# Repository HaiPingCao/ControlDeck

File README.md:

# ControlDeck

ControlDeck is a simple, multi-purpose, programmable volume knob built with an Arduino Pro Micro.  
It is designed as a compact hardware control interface for volume adjustment, mode switching, and custom hotkeys.

## Hardware

The project uses the following components:

- Arduino Pro Micro
- Rotary encoder with integrated push button
- 4 momentary push buttons
- SSD1306 OLED display (128×64)

### Circuit Setup and Wiring

| Component   | Pin | Description                                  |
| ----------- | --- | -------------------------------------------- |
| Encoder CLK | 5   | Clock signal for rotation detection          |
| Encoder DT  | 4   | Data signal for rotation direction detection |
| Encoder SW  | 6   | Encoder push button                          |
| UP Button   | 10  | Switch to previous mode                      |
| DOWN Button | 16  | Switch to next mode                          |
| # Button    | 14  | Special function button                      |
| \* Button   | 15  | Triggers Win + Ctrl + Alt + F5 hotkey        |

## Software

### Required Libraries

When using the Arduino IDE, install the following libraries via the Arduino Library Manager:

- **HID-Project** by NicoHood
- **Adafruit GFX Library** by Adafruit
- **Adafruit SSD1306** by Adafruit

### Driver Development

A new custom driver written in Rust is currently in early development to support more advanced features.  
See the `mk-driver` directory for details.

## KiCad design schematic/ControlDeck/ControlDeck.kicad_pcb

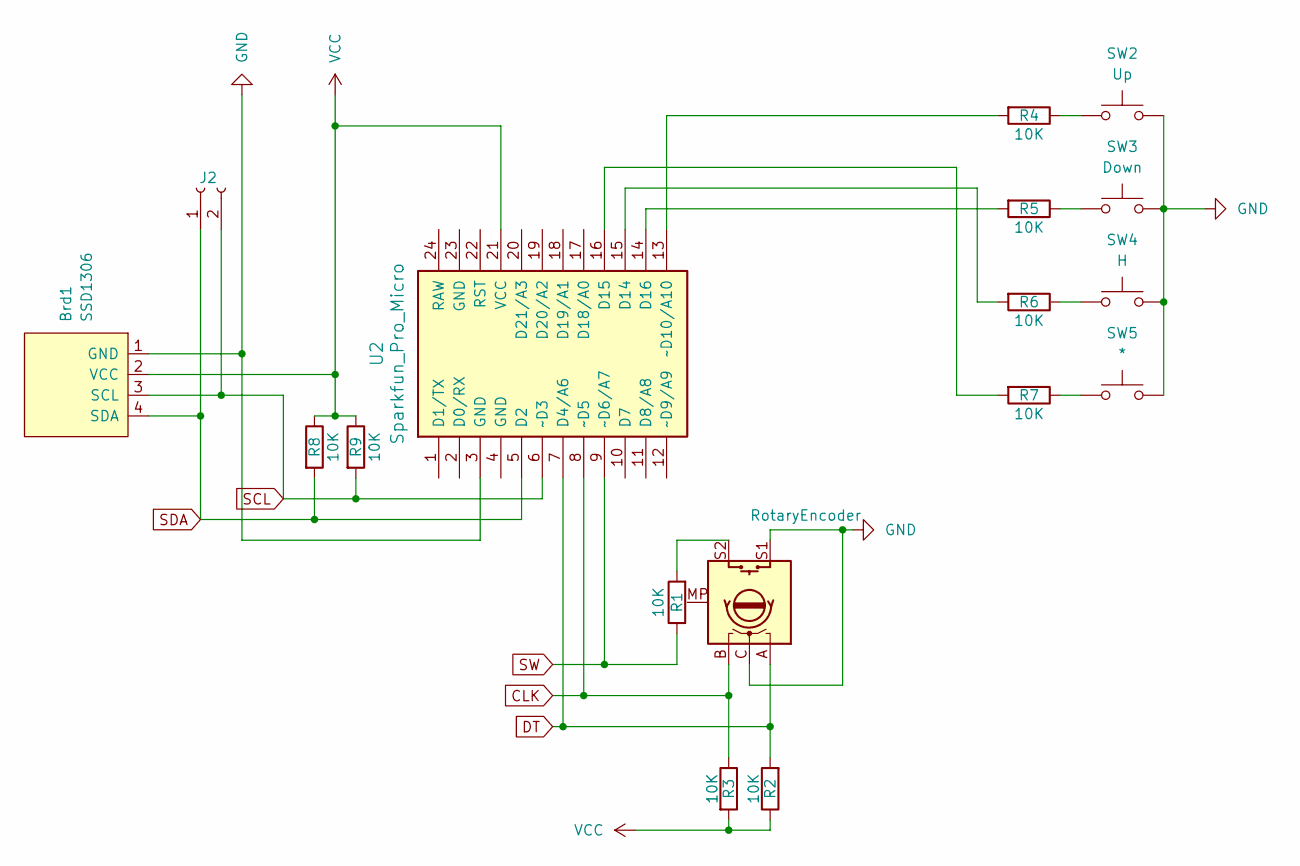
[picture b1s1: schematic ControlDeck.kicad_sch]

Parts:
Brd1: SSD1306; 128x64OLED
J2: Conn_01x02_Socket; JST_PH_B2B-PH-K_1x02_P2.00mm_Vertical
R1, R2, R3, R4, R5, R6, R7, R8, R9: 10K; R_Axial_DIN0204_L3.6mm_D1.6mm_P5.08mm_Horizontal
SW1: RotaryEncoder; RotaryEncoder_Alps_EC11E-Switch_Vertical_H20mm
SW2: Up; SW_SPST_CK_RS282G05A3
SW3: Down; SW_SPST_CK_RS282G05A3
SW4: H; SW_SPST_CK_RS282G05A3
SW5: *; SW_SPST_CK_RS282G05A3
U2: Sparkfun_Pro_Micro

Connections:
CLK: R3.1, SW1.B, U2.8 (~D5)
DT: R2.2, SW1.A, U2.7 (D4/A6)
GND: Brd1.1 (GND), SW1.C, SW1.S1, SW2.2, SW3.2, SW4.2, SW5.2, U2.3 (GND), U2.23 (GND)
unnamed: R1.2, SW1.S2
unnamed: R4.1, SW2.1
unnamed: R5.1, SW3.1
unnamed: R6.1, SW4.1
unnamed: R7.1, SW5.1
unnamed: R6.2, U2.15 (D14)
unnamed: R7.2, U2.16 (D15)
unnamed: R5.2, U2.14 (D16)
unnamed: R4.2, U2.13 (~D10/A10)
SCL: Brd1.3 (SCL), J2.2, R9.2, U2.6 (~D3)
SDA: Brd1.4 (SDA), J2.1, R8.2, U2.5 (D2)
SW: R1.1, U2.9 (~D6/A7)
VCC: Brd1.2 (VCC), R2.1, R3.2, R8.1, R9.1, U2.21 (VCC)

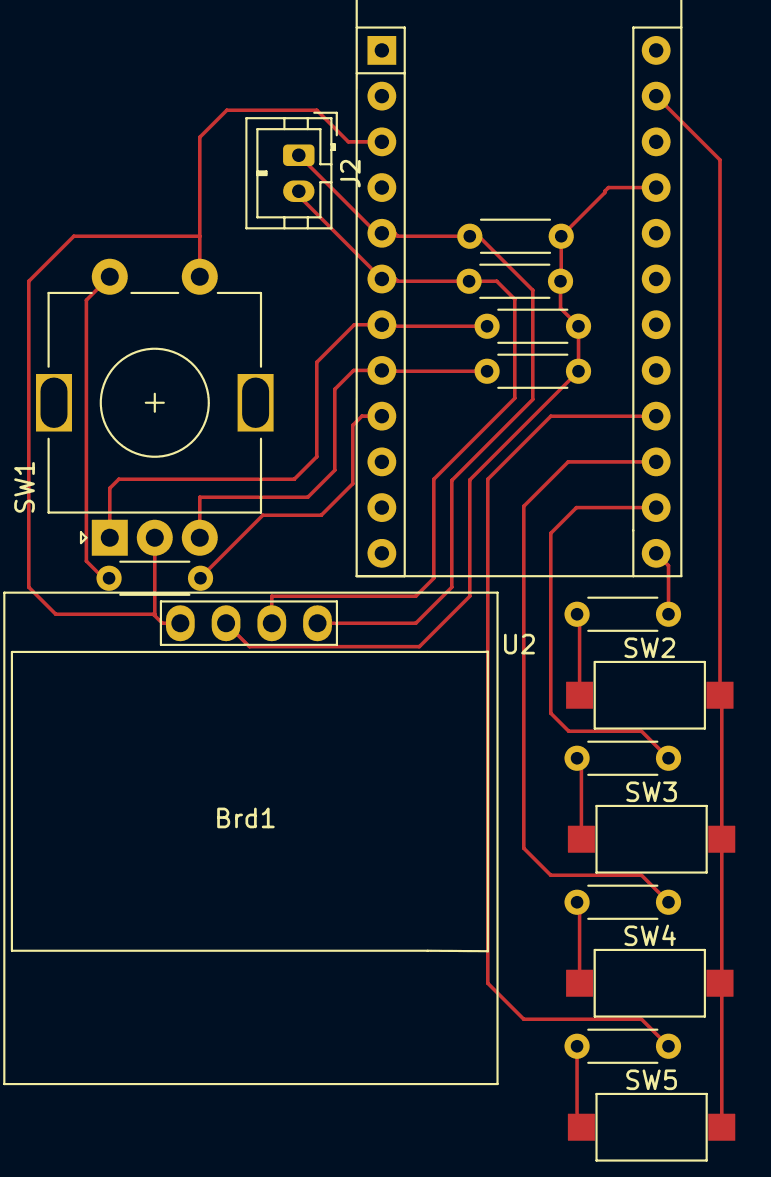
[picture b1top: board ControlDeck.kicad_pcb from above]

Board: 2 copper layers, 17 parts (0 on the bottom side), 16 nets.

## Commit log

2025-10-08 Refactor and add Win+Ctrl+Alt+F5 hotkey support
    Reorganized code with section comments for clarity and maintainability. Added support for triggering the Win+Ctrl+Alt+F5 hotkey via BTN_SCR_MODE, including OLED feedback. Improved debounce handling a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
2025-11-13 modified: VolumeKnob/VolumeKnob.ino
2026-01-01 Please enter the commit message for your changes. Lines starting with '#' will be ignored, and an empty message aborts the commit.
    On branch v1
    Your branch is up to date with 'origin/v1'.
    Changes to be committed:
    modified: .gitignore
    deleted: MacroKnob/fp-lib-table
    modified: README.md
2026-01-01 Update readme.md, change file structure, change 4 pin connector to 2 pin in circuit schematic, update code
